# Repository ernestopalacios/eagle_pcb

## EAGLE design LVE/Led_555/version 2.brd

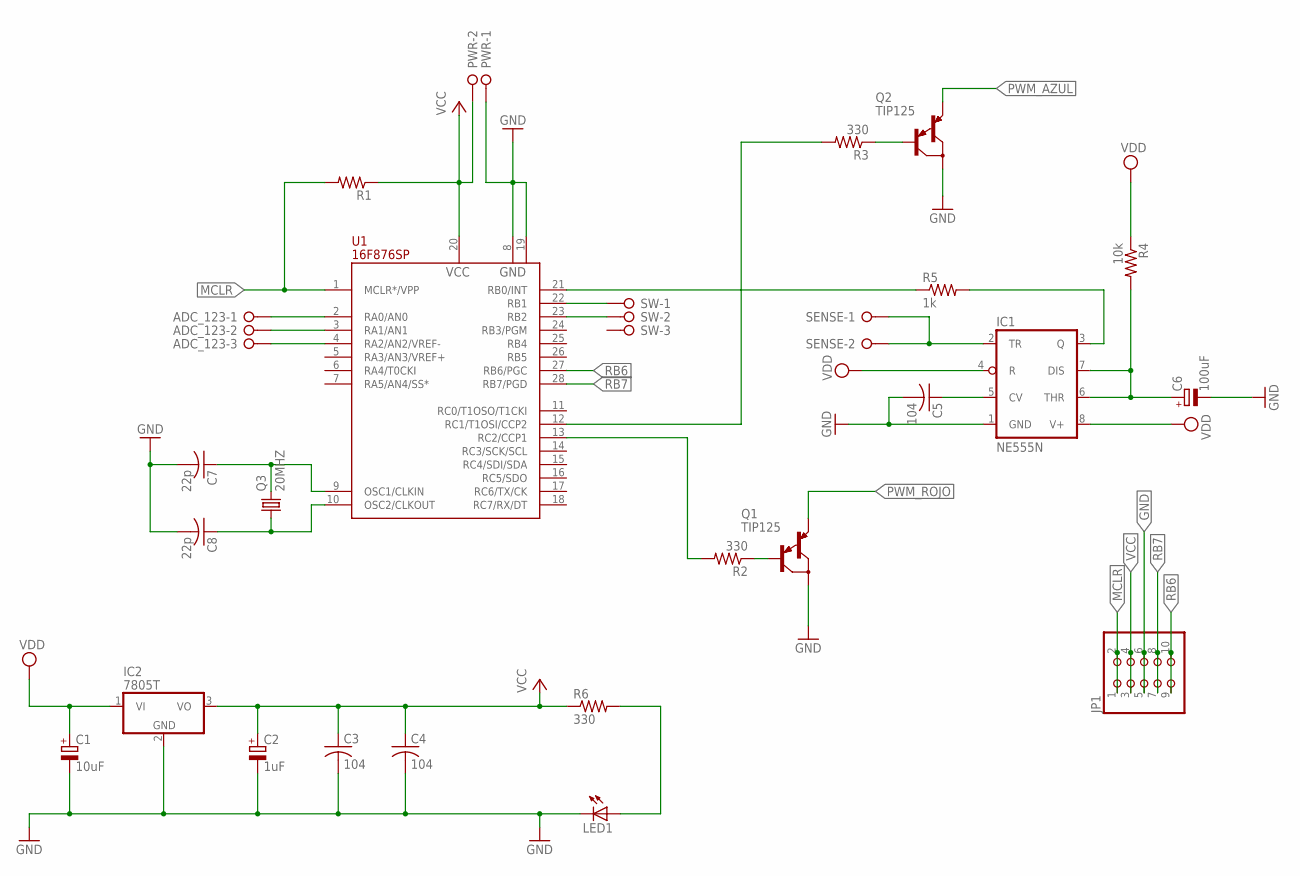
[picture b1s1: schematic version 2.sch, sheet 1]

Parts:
ADC_123: W237-03P; W237-133
C1: 10uF; E2,5-6
C2: 1uF; E2,5-6
C3, C4, C5: 104; C025-024X044
C6: 100uF; E2,5-6
C7, C8: 22p; C025-024X044
IC1: NE555N; DIL08
IC2: 7805T; TO220H
JP1: PINHD-2X5; 2X05
LED1: LED3MM
PWR: W237-02P; W237-132
Q1, Q2: TIP125; TO220
Q3: 20MHZ; HC49/S
R1: R-US_0204/7; 0204/7
R2, R3, R6: 330; 0204/7
R4: 10k; 0204/7
R5: 1k; 0204/7
SENSE: W237-02P; W237-132
SW: W237-03P; W237-133
U1: 16F876SP; DIL28-3

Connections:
GND: C1.-, C2.-, C3.2, C4.2, C5.2, C6.-, C7.2, C8.2, IC1.1 (GND), IC2.2 (GND), JP1.5, JP1.6, LED1.K (C), PWR.1, Q1.2 (C), Q2.2 (C), U1.8 (GND), U1.19 (GND); also elsewhere on the board
MCLR: JP1.1, JP1.2, R1.2, U1.1 (MCLR*/VPP)
unnamed: C5.1, IC1.5 (CV)
unnamed 3: U1.24 (RB3/PGM); also elsewhere on the board
unnamed: R2.2, U1.13 (RC2/CCP1)
unnamed: C6.+, IC1.6 (THR), IC1.7 (DIS), R4.2
unnamed: IC1.3 (Q), R5.2
unnamed: R5.1, U1.21 (RB0/INT)
unnamed: Q1.1 (B), R2.1
unnamed: IC1.2 (TR), SENSE.1, SENSE.2
unnamed: R3.2, U1.12 (RC1/T1OSI/CCP2)
unnamed: Q2.1 (B), R3.1
unnamed 14: SW.1, U1.22 (RB1); also elsewhere on the board
unnamed 15: SW.2, U1.23 (RB2); also elsewhere on the board
unnamed: ADC_123.1, U1.2 (RA0/AN0)
unnamed: ADC_123.2, U1.3 (RA1/AN1)
unnamed: ADC_123.3, U1.4 (RA2/AN2/VREF-)
unnamed: LED1.A, R6.2
unnamed: C7.1, Q3.2, U1.9 (OSC1/CLKIN)
unnamed: C8.1, Q3.1, U1.10 (OSC2/CLKOUT)
PWM_AZUL: Q2.3 (E); also elsewhere on the board
PWM_ROJO: Q1.3 (E); also elsewhere on the board
RB6: JP1.9, JP1.10, U1.27 (RB6/PGC)
RB7: JP1.7, JP1.8, U1.28 (RB7/PGD)
VCC: C2.+, C3.1, C4.1, IC2.3 (VO), JP1.3, JP1.4, PWR.2, R1.1, R6.1, U1.20 (VCC)
VDD: C1.+, IC1.4 (R), IC1.8 (V+), IC2.1 (VI), R4.1; also elsewhere on the board

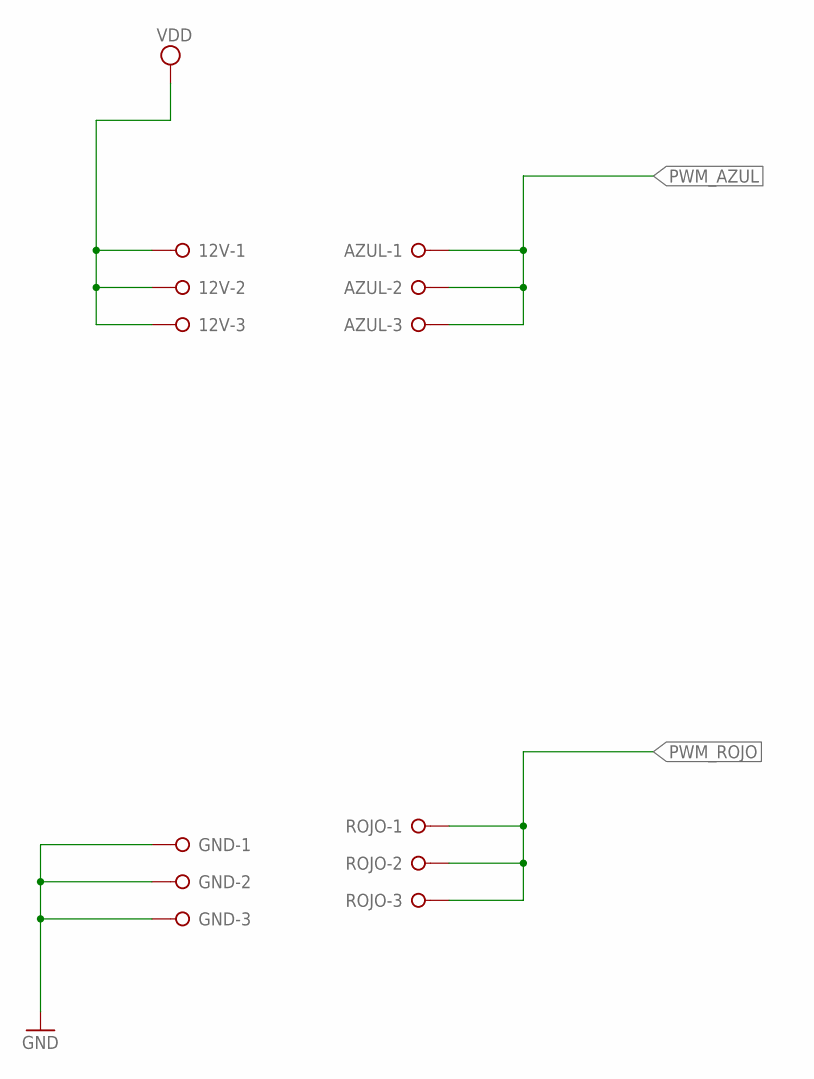
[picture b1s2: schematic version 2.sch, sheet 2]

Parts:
12V: W237-03P; W237-133
AZUL: W237-03P; W237-133
GND: W237-03P; W237-133
ROJO: W237-03P; W237-133

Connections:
GND: GND.1, GND.2, GND.3; also elsewhere on the board
PWM_AZUL: AZUL.1, AZUL.2, AZUL.3; also elsewhere on the board
PWM_ROJO: ROJO.1, ROJO.2, ROJO.3; also elsewhere on the board
VDD: 12V.1, 12V.2, 12V.3; also elsewhere on the board

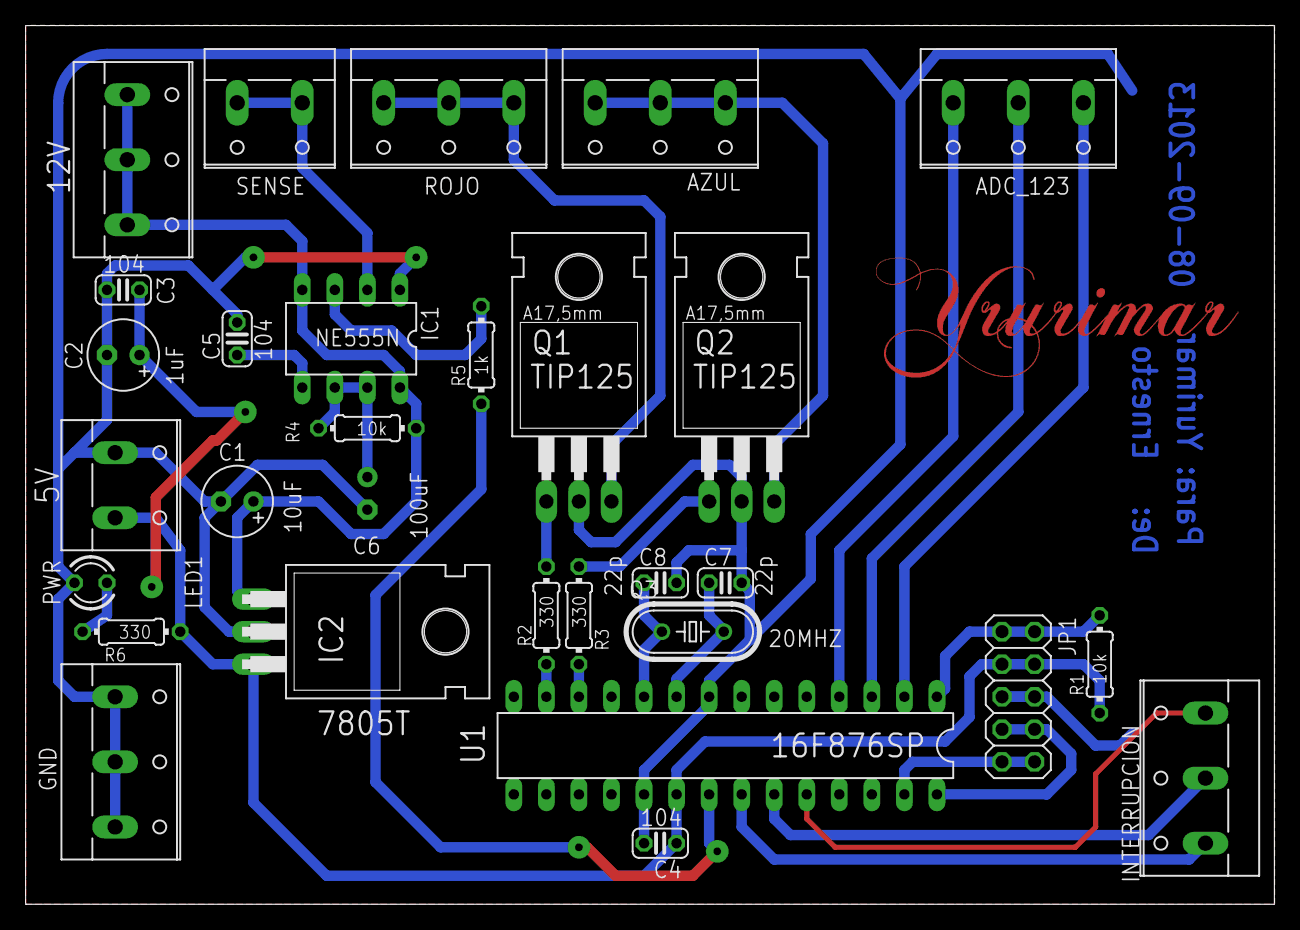
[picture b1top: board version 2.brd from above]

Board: 2 copper layers, 97.5 x 68.6 mm, 30 parts (1 on the bottom side), 26 nets.

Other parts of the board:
INTERRUPCION: W237-133

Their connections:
unnamed 3: INTERRUPCION.3; also elsewhere on the board
unnamed 14: INTERRUPCION.1; also elsewhere on the board
unnamed 15: INTERRUPCION.2; also elsewhere on the board

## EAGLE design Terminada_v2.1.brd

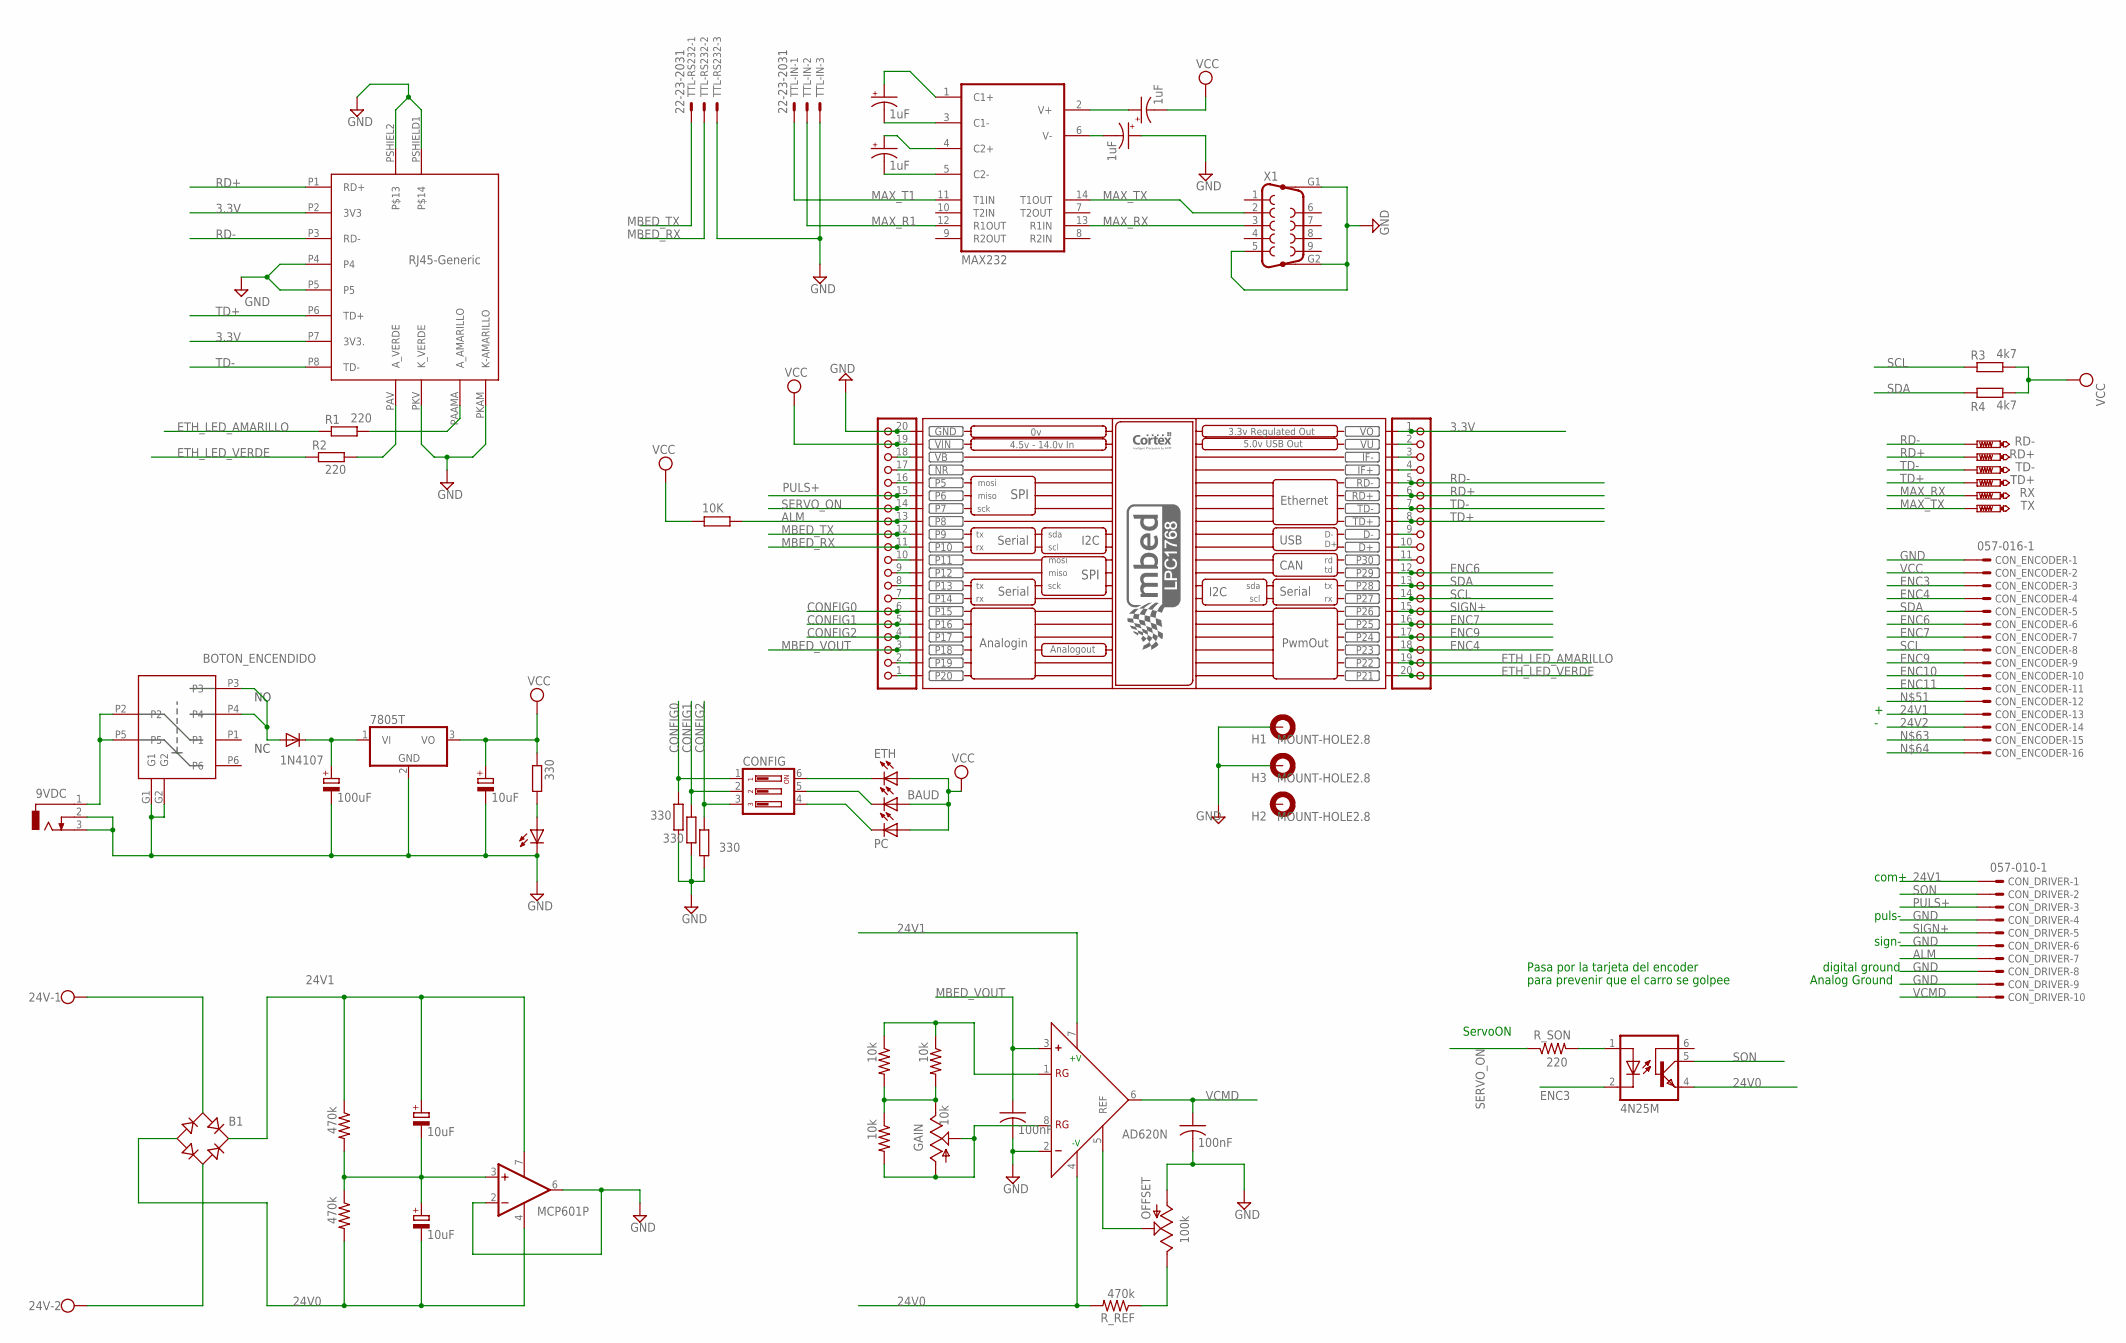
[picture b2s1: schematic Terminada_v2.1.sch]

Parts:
9VDC: DCJ0303
24V: W237-02P; W237-132
B1: RB1A
BAUD: LED3MM
C1_9V: 100uF; TT5D7
C1_+24, C2_0V, C2_9V: 10uF; TT5D7
C1_MAX, C2_MAX, C3_MAX, C4_MAX: 1uF; E2,5-6E
C3_AOUT, C5_AOUT: 100nF; C025-024X044
CONFIG: DIP03YL
CON_DRIVER: 057-010-1
CON_ENCODER: 057-016-1
D1_INPUT: 1N4107; DO35-10
ETH: LED3MM
GAIN: 10k; RJ9W
H1, H2, H3: MOUNT-HOLE2.8; 3,3-PAD
IC1: MAX232; DIL16
IC2: 7805T; TO220H
IC3: MCP601P; DIL08
IC4: AD620N; DIL08
JP_LEFT: PINHD-1X20; 1X20
JP_RIGHT: PINHD-1X20; 1X20
KIT1: MBED_NXP_LPC1768; MBED-KIT
OFFSET: 100k; RJ9W
OK1: 4N25M; DIL06
ON/OFF: BOTON_ENCENDIDO; BOTON_ENCNEDIDO
PC: LED3MM
POWER: LED3MM
PWR_LED_R: 330; 0204/7
R1, R2: 220; 0207/15
R1_DIV, R2_DIV: 470k; 0207/10
R1_G, R2_G, R3_G: 10k; 0204/7
R3, R4: 4k7; 0204/7
R13, R14, R15: 330; 0204/7
R16_ALM: 10K; 0207/12
RD+: PTR1PAD1-13Y; P1-13Y
RD-: PTR1PAD1-13Y; P1-13Y
RX: PTR1PAD1-13Y; P1-13Y
R_REF: 470k; 0204/7
R_SON: 220; 0207/7
TD+: PTR1PAD1-13Y; P1-13Y
TD-: PTR1PAD1-13Y; P1-13Y
TTL-IN: 22-23-2031
TTL-RS232: 22-23-2031
TX: PTR1PAD1-13Y; P1-13Y
U$1: RJ-45-GENERIC; RJ45-GENERIC
X1: F09HP

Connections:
3.3V: JP_RIGHT.1, KIT1.VOUT (VO), U$1.P2 (3V3), U$1.P7 (3V3.)
24V0: B1.-, C2_0V.-, IC3.4 (V-), IC4.4 (-V), OK1.4 (EMI), R2_DIV.2, R_REF.2
24V1: B1.+, C1_+24.+, CON_DRIVER.1, CON_ENCODER.13, IC3.7 (V+), IC4.7 (+V), R1_DIV.1
24V2: CON_ENCODER.14
ALM: CON_DRIVER.7, JP_LEFT.13, KIT1.P$8 (P8), R16_ALM.1
CONFIG0: CONFIG.1, JP_LEFT.6, KIT1.P$15 (P15), R15.2
CONFIG1: CONFIG.2, JP_LEFT.5, KIT1.P$16 (P16), R14.2
CONFIG2: CONFIG.3, JP_LEFT.4, KIT1.P$17 (P17), R13.2
ENC3: CON_ENCODER.3, OK1.2 (C)
ENC4: CON_ENCODER.4, JP_RIGHT.18, KIT1.P$23 (P23)
ENC6: CON_ENCODER.6, JP_RIGHT.12, KIT1.P$29 (P29)
ENC7: CON_ENCODER.7, JP_RIGHT.16, KIT1.P$25 (P25)
ENC9: CON_ENCODER.9, JP_RIGHT.17, KIT1.P$24 (P24)
ENC10: CON_ENCODER.10
ENC11: CON_ENCODER.11
ETH_LED_AMARILLO: JP_RIGHT.19, KIT1.P$22 (P22), R1.1
ETH_LED_VERDE: JP_RIGHT.20, KIT1.P$21 (P21), R2.1
GND: 9VDC.2, 9VDC.3, C1_9V.-, C2_9V.-, C3_AOUT.2, C3_MAX.+, C5_AOUT.2, CON_DRIVER.4, CON_DRIVER.6, CON_DRIVER.8, CON_DRIVER.9, CON_ENCODER.1, H1.B3,3, H3.B3,3, IC1.15 (GND), IC2.2 (GND), IC3.2 (-IN), IC3.6 (OUT), IC4.2 (-), JP_LEFT.20, KIT1.GND, OFFSET.A, ON/OFF.G1, ON/OFF.G2, POWER.K (C), R13.1, R14.1, R15.1, TTL-IN.3, TTL-RS232.3, U$1.P4, U$1.P5, U$1.PKAM (K-AMARILLO), U$1.PKV (K_VERDE), U$1.PSHIEL2, U$1.PSHIELD1, X1.5, X1.G1, X1.G2
MAX_R1: IC1.12 (R1OUT), TTL-IN.2
MAX_RX: IC1.13 (R1IN), RX.TP, X1.3
MAX_T1: IC1.11 (T1IN), TTL-IN.1
MAX_TX: IC1.14 (T1OUT), TX.TP, X1.2
MBED_RX: JP_LEFT.11, KIT1.P$10 (P10), TTL-RS232.2
MBED_TX: JP_LEFT.12, KIT1.P$9 (P9), TTL-RS232.1
MBED_VOUT: C5_AOUT.1, IC4.3 (+), JP_LEFT.3, KIT1.P$18 (P18)
unnamed: 24V.1, B1.AC1
unnamed: 24V.2, B1.AC2
unnamed: C1_+24.-, C2_0V.+, IC3.3 (+IN), R1_DIV.2, R2_DIV.1
unnamed: JP_RIGHT.2, KIT1.VU
unnamed: JP_RIGHT.3, KIT1.IF-
unnamed: OFFSET.E, R_REF.1
unnamed: IC4.1 (RG), R1_G.1, R3_G.1
unnamed: GAIN.E, R1_G.2, R2_G.1, R3_G.2
unnamed: GAIN.A, GAIN.S, IC4.8 (RG), R2_G.2
unnamed: D1_INPUT.A, ON/OFF.P3, ON/OFF.P4
unnamed: JP_RIGHT.4, KIT1.IF+
unnamed: IC4.5 (REF), OFFSET.S
unnamed: JP_RIGHT.11, KIT1.P$30 (P30)
unnamed: 9VDC.1, ON/OFF.P2, ON/OFF.P5
unnamed: OK1.1 (A), R_SON.2
unnamed: C1_9V.+, D1_INPUT.C, IC2.1 (VI)
unnamed: CONFIG.6, ETH.K (C)
unnamed: BAUD.K (C), CONFIG.5
unnamed: CONFIG.4, PC.K (C)
unnamed: JP_RIGHT.9, KIT1.D-
unnamed: JP_RIGHT.10, KIT1.D+
unnamed: C1_MAX.+, IC1.1 (C1+)
unnamed: C1_MAX.-, IC1.3 (C1-)
unnamed: C2_MAX.-, IC1.5 (C2-)
unnamed: C2_MAX.+, IC1.4 (C2+)
unnamed: C4_MAX.+, IC1.2 (V+)
unnamed: C3_MAX.-, IC1.6 (V-)
unnamed: R1.2, U$1.PAAMA (A_AMARILLO)
unnamed: JP_LEFT.18, KIT1.VB
unnamed: JP_LEFT.17, KIT1.NR
unnamed: JP_LEFT.16, KIT1.P$5 (P5)
unnamed: R2.2, U$1.PAV (A_VERDE)
unnamed: JP_LEFT.10, KIT1.P$11 (P11)
unnamed: JP_LEFT.9, KIT1.P$12 (P12)
unnamed: JP_LEFT.8, KIT1.P$13 (P13)
unnamed: JP_LEFT.7, KIT1.P$14 (P14)
unnamed: JP_LEFT.2, KIT1.P$19 (P19)
unnamed: JP_LEFT.1, KIT1.P$20 (P20)
unnamed: POWER.A, PWR_LED_R.2
PULS+: CON_DRIVER.3, JP_LEFT.15, KIT1.P$6 (P6)
RD+: JP_RIGHT.6, KIT1.RD+, RD+.TP, U$1.P1 (RD+)
RD-: JP_RIGHT.5, KIT1.RD-, RD-.TP, U$1.P3 (RD-)
SCL: CON_ENCODER.8, JP_RIGHT.14, KIT1.P$27 (P27), R3.1
SDA: CON_ENCODER.5, JP_RIGHT.13, KIT1.P$28 (P28), R4.1
SERVO_ON: JP_LEFT.14, KIT1.P$7 (P7), R_SON.1
SIGN+: CON_DRIVER.5, JP_RIGHT.15, KIT1.P$26 (P26)
SON: CON_DRIVER.2, OK1.5 (COL)
TD+: JP_RIGHT.8, KIT1.TD+, TD+.TP, U$1.P6 (TD+)
TD-: JP_RIGHT.7, KIT1.TD-, TD-.TP, U$1.P8 (TD-)
VCC: BAUD.A, C2_9V.+, C4_MAX.-, CON_ENCODER.2, ETH.A, IC1.16 (VCC), IC2.3 (VO), JP_LEFT.19, KIT1.VIN, PC.A, PWR_LED_R.1, R3.2, R4.2, R16_ALM.2
VCMD: C3_AOUT.1, CON_DRIVER.10, IC4.6 (OUT)

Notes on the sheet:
ServoON
Pasa por la tarjeta del encoder
para prevenir que el carro se golpee
Analog Ground
com+
puls-
sign-
digital ground

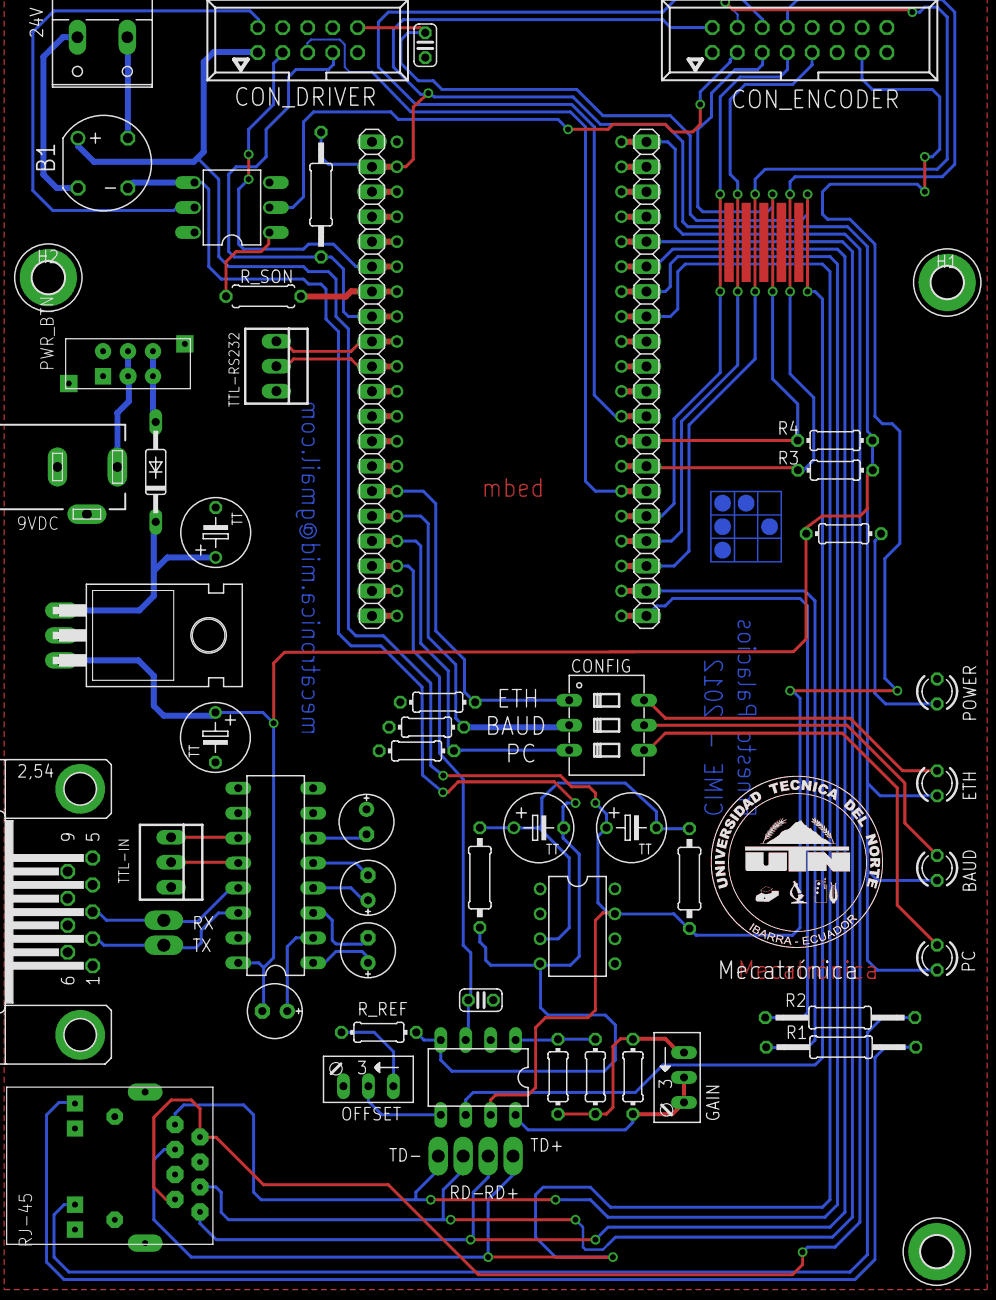
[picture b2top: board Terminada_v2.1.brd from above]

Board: 2 copper layers, 61 parts (0 on the bottom side), 73 nets.

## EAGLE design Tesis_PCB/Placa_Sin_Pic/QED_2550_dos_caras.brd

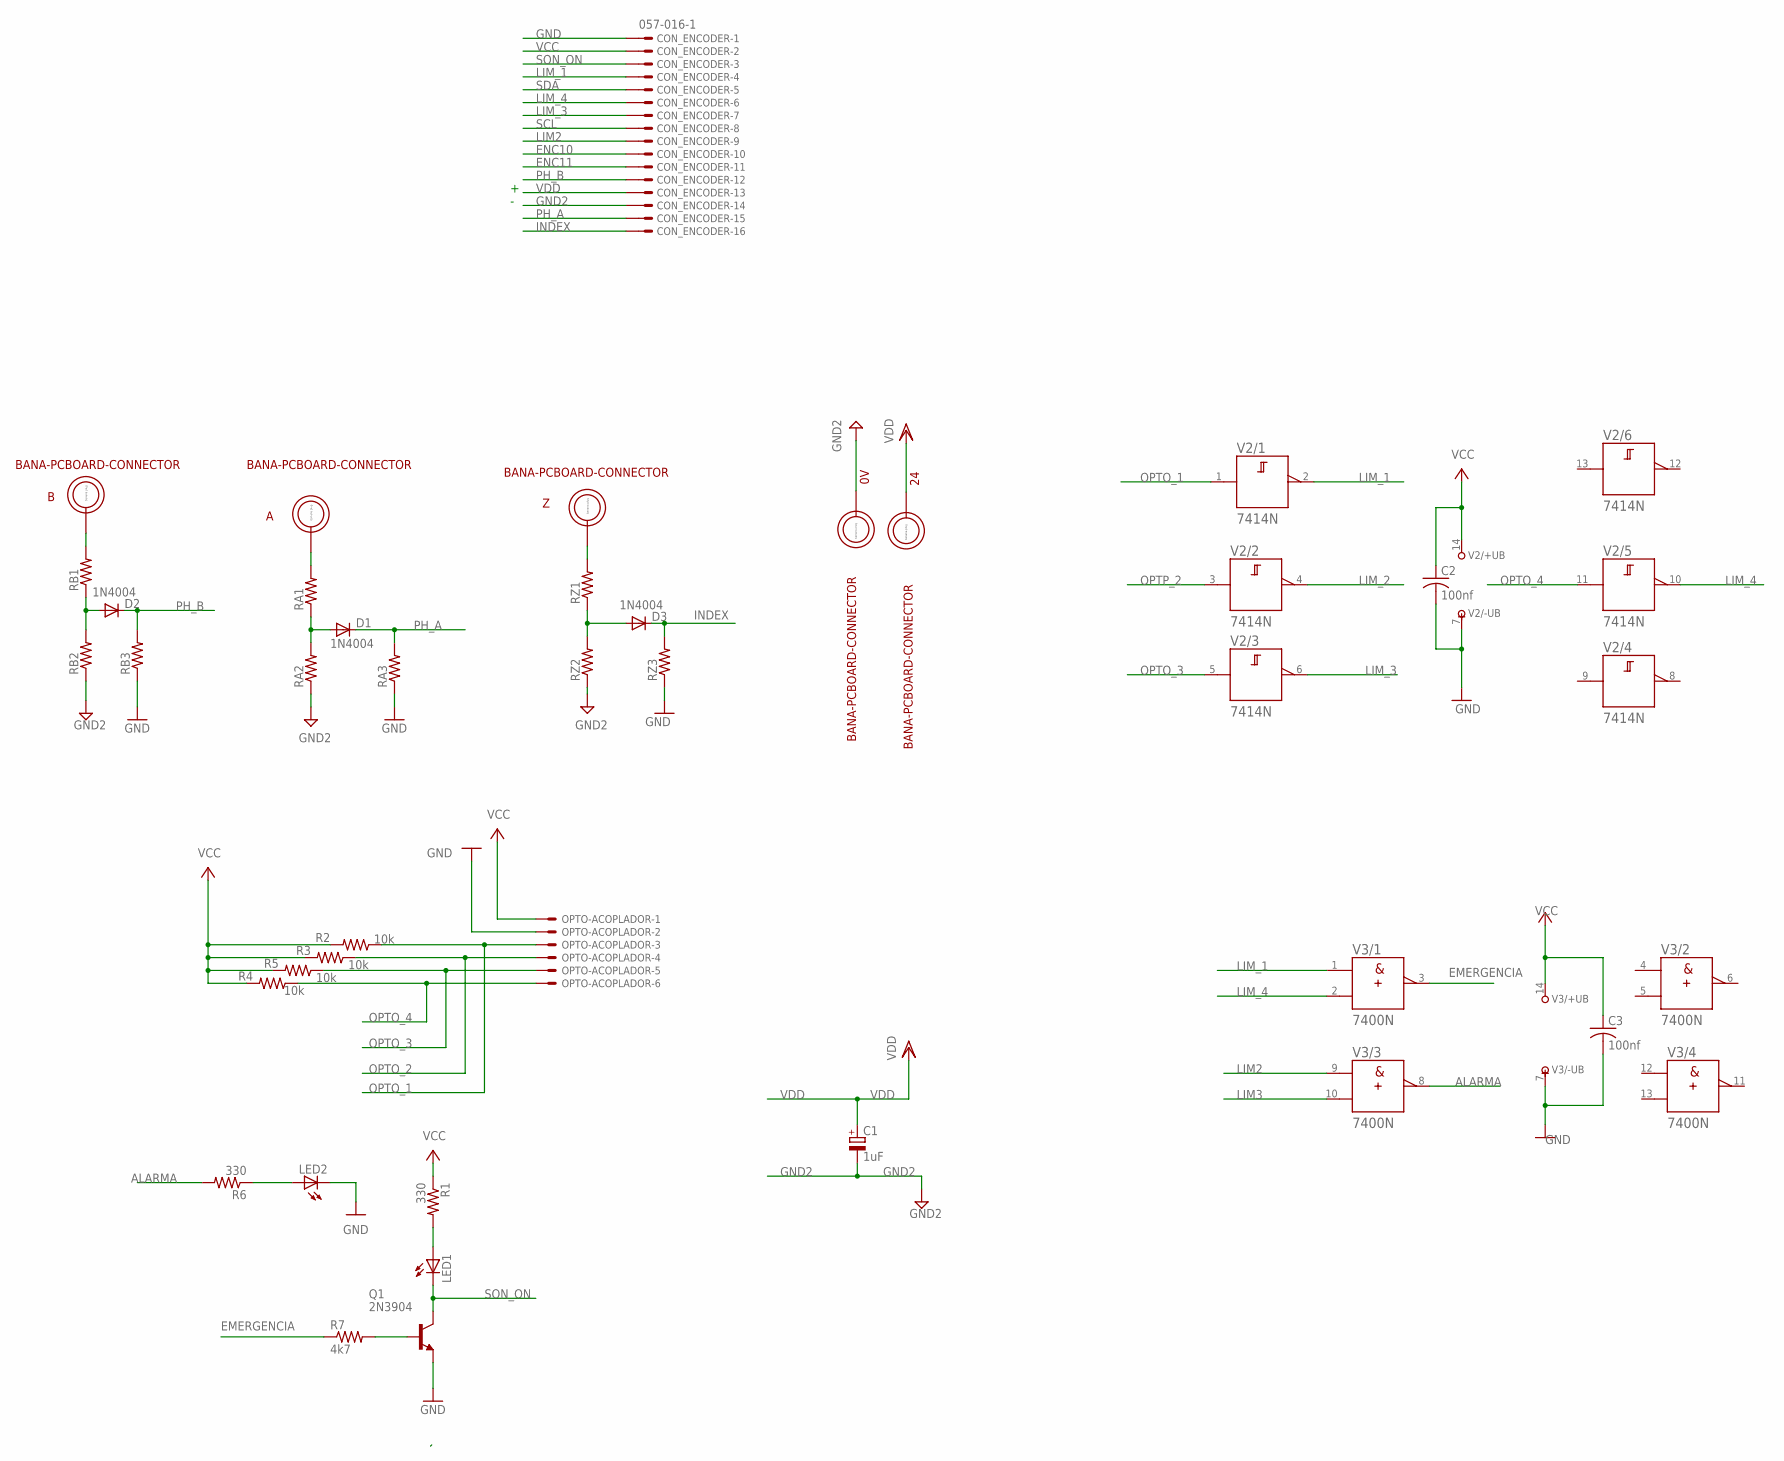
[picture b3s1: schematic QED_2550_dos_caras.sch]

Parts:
0V, 24: BANA-PCBOARD-CONNECTOR; BANA_PLUG
A: BANA-PCBOARD-CONNECTOR; BANA_PLUG
B: BANA-PCBOARD-CONNECTOR; BANA_PLUG
C1: 1uF; E2,5-6
C2, C3: 100nf; C025-024X044
CON_ENCODER: 057-016-1
D1, D2, D3: 1N4004; DO41-10
LED1, LED2: LED5MM
OPTO-ACOPLADOR: 22-23-2061
Q1: 2N3904; TO92
R1, R6: 330; 0204/7
R2, R3, R4, R5: 10k; 0204/7
R7: 4k7; 0204/7
RA1, RA2, RA3: R-US_0204/7; 0204/7
RB1, RB2, RB3: R-US_0204/7; 0204/7
RZ1, RZ2, RZ3: R-US_0204/7; 0204/7
V2: 7414N; DIL14
V3: 7400N; DIL14
Z: BANA-PCBOARD-CONNECTOR; BANA_PLUG

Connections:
ALARMA: R6.2, V3.8 (Y)
EMERGENCIA: R7.1, V3.3 (Y)
ENC10: CON_ENCODER.10
ENC11: CON_ENCODER.11
GND: C2.2, C3.2, CON_ENCODER.1, LED2.K (C), OPTO-ACOPLADOR.2, Q1.3 (E), RA3.1, RB3.1, RZ3.1, V2.7 (-UB), V3.7 (-UB)
GND2: 0V.P$1, C1.-, CON_ENCODER.14, RA2.1, RB2.1, RZ2.1
INDEX: CON_ENCODER.16, D3.C, RZ3.2
LIM2: CON_ENCODER.9, V3.9 (A)
LIM3: V3.10 (B)
LIM_1: CON_ENCODER.4, V2.2 (Y), V3.1 (A)
LIM_2: V2.4 (Y)
LIM_3: CON_ENCODER.7, V2.6 (Y)
LIM_4: CON_ENCODER.6, V2.10 (Y), V3.2 (B)
unnamed: Q1.2 (B), R7.2
unnamed: LED1.A, R1.2
unnamed: LED2.A, R6.1
unnamed: D1.A, RA1.1, RA2.2
unnamed: D2.A, RB1.1, RB2.2
unnamed: RZ1.2, Z.P$1
unnamed: B.P$1, RB1.2
unnamed: A.P$1, RA1.2
unnamed: D3.A, RZ1.1, RZ2.2
OPTO_1: OPTO-ACOPLADOR.3, R2.1, V2.1 (A)
OPTO_2: OPTO-ACOPLADOR.4, R3.1
OPTO_3: OPTO-ACOPLADOR.5, R5.1, V2.5 (A)
OPTO_4: OPTO-ACOPLADOR.6, R4.1, V2.11 (A)
OPTP_2: V2.3 (A)
PH_A: CON_ENCODER.15, D1.C, RA3.2
PH_B: CON_ENCODER.12, D2.C, RB3.2
SCL: CON_ENCODER.8
SDA: CON_ENCODER.5
SON_ON: CON_ENCODER.3, LED1.K (C), Q1.1 (C)
VCC: C2.1, C3.1, CON_ENCODER.2, OPTO-ACOPLADOR.1, R1.1, R2.2, R3.2, R4.2, R5.2, V2.14 (+UB), V3.14 (+UB)
VDD: 24.P$1, C1.+, CON_ENCODER.13

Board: 2 copper layers, 34 parts (0 on the bottom side), 27 nets, no tracks yet.
